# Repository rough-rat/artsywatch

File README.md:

# artsywatch

## Licensing Note

This project uses footprints, symbols and and 3D models converted via the
[easy2kicad](https://github.com/uPesy/easyeda2kicad.py) project.
These are derived from publicly available EasyEDA/JLCPCB component data,
used here solely to support reproducibility of this open hardware design.
All trademarks and component data belong to their respective owners.

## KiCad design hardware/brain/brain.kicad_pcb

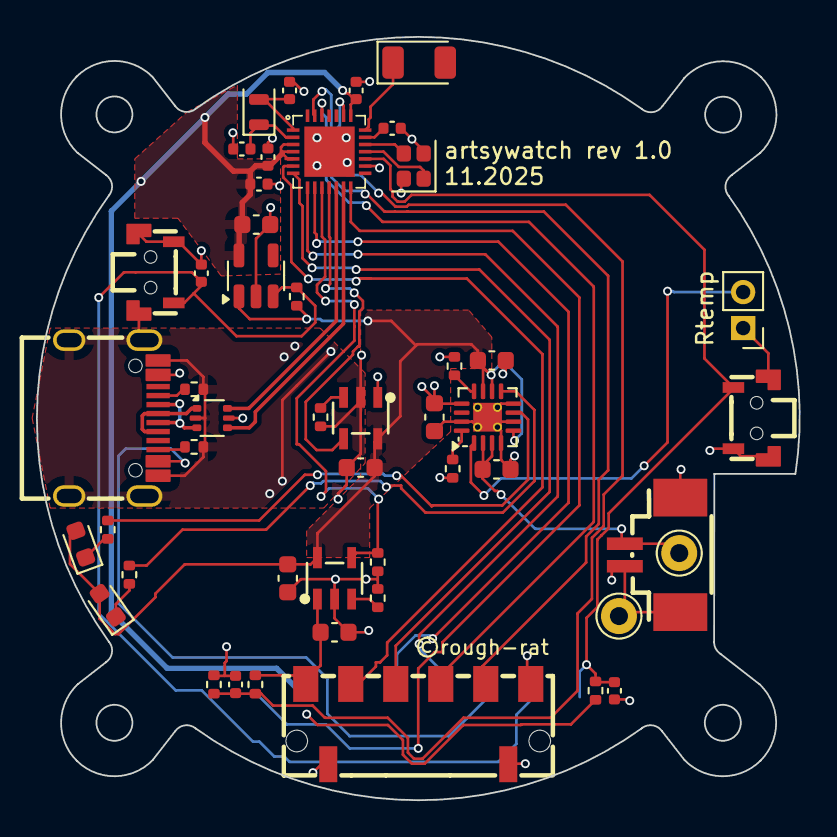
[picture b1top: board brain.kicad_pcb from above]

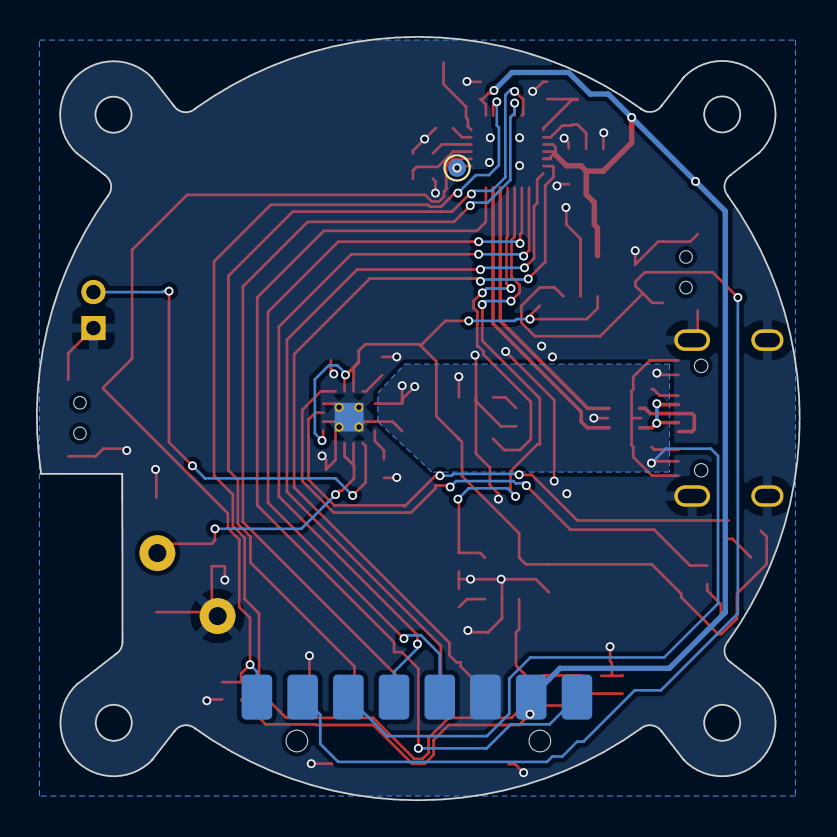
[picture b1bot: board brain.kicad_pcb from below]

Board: 2 copper layers, 42.4 x 42.4 mm, 50 parts (2 on the bottom side), 40 nets.

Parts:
AE1: Antenna_Chip; Johanson_2450AT18x100
C1, C4, C5, C6, C7, C8, C20: 10u; C_0603_1608Metric
C9, C13, C15, C17: 100n; C_0402_1005Metric
C11, C12, C14: 2.2uF; C_0402_1005Metric
C18, C19: 12p; C_0402_1005Metric
CN1: GT-BTP25006-0300A-010A; CONN-SMD_GT-BTP25006-0300A-010A
D1: LED_WHITE; LED_0603_1608Metric
D2: LED_RED; LED_0603_1608Metric
J5: Conn_01x08; PinSocket_1x08_P2.54mm_Vertical
P1: 1.25T-2PWT; CONN-SMD_P1.25-H_1.25T-2PWT
R1, R3: 5.1k; R_0402_1005Metric
R2, R4, R5, R12, R17, R20: 10k; R_0402_1005Metric
R6, R7: 3k; R_0402_1005Metric
R10, R11, R13: 100k; R_0402_1005Metric
SW1, SW2: TS24CA; SW-SMD_2P-TS24CA
TP1, TP2: TestPoint; Pin_D1.0mm_L10.0mm
TP3: TestPoint_2Pole; PinHeader_1x02_P2.00mm_Vertical
TP4: RX; TestPoint_Pad_D1.0mm
U1: USBLC6-2P6; SOT-666
U2: SPX3819M5-L-3-3; SOT-23-5
U3: BQ24073RGT; VQFN-16-1EP_3x3mm_P0.5mm_EP1.6x1.6mm_ThermalVias
U4, U5: LPW5209AB5F; SOT-23-5_L3.0-W1.7-P0.95-LS2.8-BL
U6: CH582F_C3001175; QFN-28_L4.0-W4.0-P0.40-BL-EP2.8
USBC1: TYPE-C-31-M-12; USB-C_SMD-TYPE-C-31-M-12_1
Y1: XO-32K; Crystal_SMD_2012-2Pin_2.0x1.2mm
Y2: 32 MHz; Crystal_SMD_2016-4Pin_2.0x1.6mm

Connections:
+4V: C4.1, C7.1, C20.1, D1.2 (A), D2.2 (A), R2.1, U2.1 (IN), U3.5 (EN2), U3.10 (OUT), U3.11 (OUT), U4.5 (VIN), U5.5 (VIN)
/4V_ENA: R11.2, U4.4 (EN), U6.10 (PB13/U2D+/SCK0_/SCL/TXD1_)
/4V_OUT: C8.1, CN1.1, R10.2, U4.1 (VOUT)
/BOOT: C17.1, J5.8, R17.1, SW2.1, U6.17 (PB22/TMR3/RXD2)
/BQ_CHG: R5.1, U3.9 (~CHG)
/BQ_PGOOD: R4.1, U3.7 (~PGOOD)
/CONN_DN: U1.3 (I/O2), USBC1.A7 (DN1), USBC1.B7 (DN2)
/CONN_DP: U1.1 (I/O1), USBC1.A6 (DP1), USBC1.B6 (DP2)
/DAT: CN1.4, U6.26 (PA14/MOSI/TXD0_/AIN4)
/LAT: CN1.3, U6.7 (PA9/TMR0/TXD1/AIN13)
/LIPO+: C6.1, P1.1, TP1.1, U3.2 (BAT), U3.3 (BAT)
/OE: CN1.2, U6.6 (PA8/RXD1/AIN12)
/PWR_CUTOFF: C15.1, J5.7, R2.2, SW1.1, U2.3 (EN)
/SCLK: CN1.5, U6.27 (PA13/SCK0/PWM5/AIN3)
/TCK: J5.5, U6.8 (PB15/TCK/MISO_/DTR_)
/TIO: J5.4, U6.9 (PB14/TIO/DSR_/MOSI_/PWM10)
/TX: J5.1, U6.14 (PB7/TXD0/PWM9)
/USB_BACKFEED_ENA: U5.4 (EN), U6.11 (PB12/U2D-/SCS_/SDA/RXD1_)
/USB_DN: U1.4 (I/O2), U6.13 (PB10/UD-/TMR1_)
/USB_DP: U1.6 (I/O1), U6.12 (PB11/UD+/TMR2_)
/VBAT_MEAS: C9.1, R10.1, R13.2, U6.23 (PA4/RXD3/AIN0)
/X32I: U6.19 (X32MI), Y2.3
/X32O: U6.18 (X32MO), Y2.1
/nRST: TP4.1, U6.16 (PB23/RST/TMR0_/TXD2_/PWM11)
GND: C1.2, C4.2, C5.2, C6.2, C7.2, C8.2, C9.2, C11.2, C12.2, C13.2, C14.1, C15.2, C17.2, C18.2, C19.2, C20.2, CN1.6, CN1.7, CN1.8, J5.3, P1.2, P1.3, P1.4, R1.2, R3.2, R6.1, R7.1, R11.1, R12.1, R13.1, R20.1, SW1.2, SW1.3, SW1.4, SW2.2, SW2.3, SW2.4, TP2.1, TP3.1, U1.2 (GND), U2.2 (GND), U3.4 (~CE), U3.6 (EN1), U3.8 (VSS), U3.15 (TD), U3.17 (VSS), U4.2 (GND), U5.2 (GND), U6.29 (EP), USBC1.1 (EH), USBC1.2 (EH), USBC1.3 (EH), USBC1.4 (EH), USBC1.A1B12 (GND), USBC1.B1A12 (GND), Y2.2, Y2.4
unnamed: AE1.1 (FEED), U6.21 (ANT)
unnamed: D1.1 (K), R4.2
unnamed: D2.1 (K), R5.2
unnamed: R6.2, U3.12 (ILIM)
unnamed: R7.2, U3.16 (ISET)
unnamed: TP3.2, U3.1 (TS)
unnamed: R12.2, U4.3 (ISET)
unnamed: R20.2, U5.3 (ISET)
unnamed: C18.1, U6.2 (PA10/X32KI/TMR1), Y1.1
unnamed: C19.1, U6.1 (PA11/X32KO/TMR2), Y1.2
unnamed: C14.2, U6.20 (VINTA)
unnamed: R3.1, USBC1.A5 (CC1)
unnamed: R1.1, USBC1.B5 (CC2)
VBUS: C1.1, J5.6, U1.5 (VBUS), U3.13 (IN), U5.1 (VOUT), USBC1.A4B9 (VBUS), USBC1.B4A9 (VBUS)
VDD: C5.1, C11.1, C12.1, C13.1, J5.2, R17.2, U2.5 (OUT), U6.3 (VDCID), U6.4 (VSW), U6.5 (VIO33/VDD33), U6.22 (VDCIA)

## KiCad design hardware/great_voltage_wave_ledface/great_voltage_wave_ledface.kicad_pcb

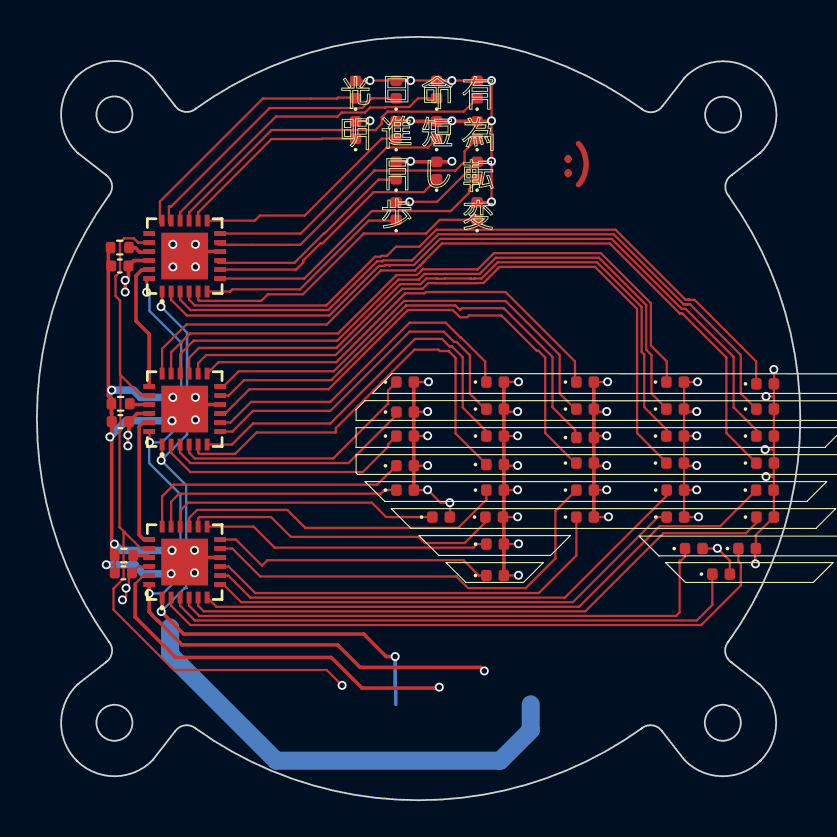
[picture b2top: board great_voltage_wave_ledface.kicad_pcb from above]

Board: 2 copper layers, 42.4 x 42.4 mm, 58 parts (1 on the bottom side), 59 nets.

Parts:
C3, C10, C16: 470n; C_0402_1005Metric
D3, D4, D5, D6, D7, D8, D9, D10, D11, D12, D13, D14, D15, D16, D17, D18, D19, D20, D21, D22, D23, D24, D25, D26, D27, D28, D29, D30, D31, D32, D33, D34, D35, D36, D37, D38, D39, D40, D41, D42, D43, D44, D45, D46, D47, D48, D49, D50: LED; LED_0402_1005Metric
J1: Conn_01x06; CONN-SMD_GT-BTP25006-0300A-010A
R14, R16, R19: 510; R_0402_1005Metric
U101, U102, U103: FM6126QC; TQFN-24_L4.0-W4.0-P0.50-BL-EP2.6

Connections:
/DAT: J1.4, U101.23 (SDI)
/LAT: J1.3, U101.1 (LE), U102.1 (LE), U103.1 (LE)
/OE: J1.2, U101.20 (OE), U102.20 (OE), U103.20 (OE)
/SCLK: J1.5, U101.24 (CLK), U102.24 (CLK), U103.24 (CLK)
GND: C3.2, C10.2, C16.2, J1.6, R14.2, R16.2, R19.2, U101.10 (GND), U101.25 (EP), U102.10 (GND), U102.25 (EP), U103.10 (GND), U103.25 (EP)
unnamed: D3.1 (K), U103.18 (~OUT15)
unnamed: D4.1 (K), U103.17 (~OUT14)
unnamed: D5.1 (K), U103.16 (~OUT13)
unnamed: D6.1 (K), U103.15 (~OUT12)
unnamed: D7.1 (K), U103.14 (~OUT11)
unnamed: D8.1 (K), U103.13 (~OUT10)
unnamed: D9.1 (K), U103.12 (~OUT9)
unnamed: D10.1 (K), U103.11 (~OUT8)
unnamed: D11.1 (K), U103.9 (~OUT7)
unnamed: D12.1 (K), U103.8 (~OUT6)
unnamed: D13.1 (K), U103.7 (~OUT5)
unnamed: D14.1 (K), U103.6 (~OUT4)
unnamed: D15.1 (K), U103.5 (~OUT3)
unnamed: D16.1 (K), U103.4 (~OUT2)
unnamed: D17.1 (K), U103.3 (~OUT1)
unnamed: D18.1 (K), U103.2 (~OUT0)
unnamed: D19.1 (K), U102.2 (~OUT0)
unnamed: D20.1 (K), U102.3 (~OUT1)
unnamed: D21.1 (K), U102.4 (~OUT2)
unnamed: D22.1 (K), U102.5 (~OUT3)
unnamed: D23.1 (K), U102.6 (~OUT4)
unnamed: D24.1 (K), U102.7 (~OUT5)
unnamed: D25.1 (K), U102.8 (~OUT6)
unnamed: D26.1 (K), U102.9 (~OUT7)
unnamed: D27.1 (K), U102.11 (~OUT8)
unnamed: D28.1 (K), U102.12 (~OUT9)
unnamed: D29.1 (K), U102.13 (~OUT10)
unnamed: D30.1 (K), U102.14 (~OUT11)
unnamed: D31.1 (K), U102.15 (~OUT12)
unnamed: D32.1 (K), U102.16 (~OUT13)
unnamed: D33.1 (K), U102.17 (~OUT14)
unnamed: D34.1 (K), U102.18 (~OUT15)
unnamed: D35.1 (K), U101.2 (~OUT0)
unnamed: D36.1 (K), U101.3 (~OUT1)
unnamed: D37.1 (K), U101.4 (~OUT2)
unnamed: D38.1 (K), U101.5 (~OUT3)
unnamed: D39.1 (K), U101.6 (~OUT4)
unnamed: D40.1 (K), U101.7 (~OUT5)
unnamed: D41.1 (K), U101.8 (~OUT6)
unnamed: D42.1 (K), U101.9 (~OUT7)
unnamed: D43.1 (K), U101.11 (~OUT8)
unnamed: D44.1 (K), U101.12 (~OUT9)
unnamed: D45.1 (K), U101.13 (~OUT10)
unnamed: D46.1 (K), U101.14 (~OUT11)
unnamed: D47.1 (K), U101.15 (~OUT12)
unnamed: D48.1 (K), U101.16 (~OUT13)
unnamed: D49.1 (K), U101.17 (~OUT14)
unnamed: D50.1 (K), U101.18 (~OUT15)
unnamed: R14.1, U101.21 (REXT)
unnamed: U101.19 (SDO), U102.23 (SDI)
unnamed: R16.1, U102.21 (REXT)
unnamed: U102.19 (SDO), U103.23 (SDI)
unnamed: R19.1, U103.21 (REXT)
VDD: C3.1, C10.1, C16.1, D3.2 (A), D4.2 (A), D5.2 (A), D6.2 (A), D7.2 (A), D8.2 (A), D9.2 (A), D10.2 (A), D11.2 (A), D12.2 (A), D13.2 (A), D14.2 (A), D15.2 (A), D16.2 (A), D17.2 (A), D18.2 (A), D19.2 (A), D20.2 (A), D21.2 (A), D22.2 (A), D23.2 (A), D24.2 (A), D25.2 (A), D26.2 (A), D27.2 (A), D28.2 (A), D29.2 (A), D30.2 (A), D31.2 (A), D32.2 (A), D33.2 (A), D34.2 (A), D35.2 (A), D36.2 (A), D37.2 (A), D38.2 (A), D39.2 (A), D40.2 (A), D41.2 (A), D42.2 (A), D43.2 (A), D44.2 (A), D45.2 (A), D46.2 (A), D47.2 (A), D48.2 (A), D49.2 (A), D50.2 (A), J1.1, U101.22 (VDD), U102.22 (VDD), U103.22 (VDD)

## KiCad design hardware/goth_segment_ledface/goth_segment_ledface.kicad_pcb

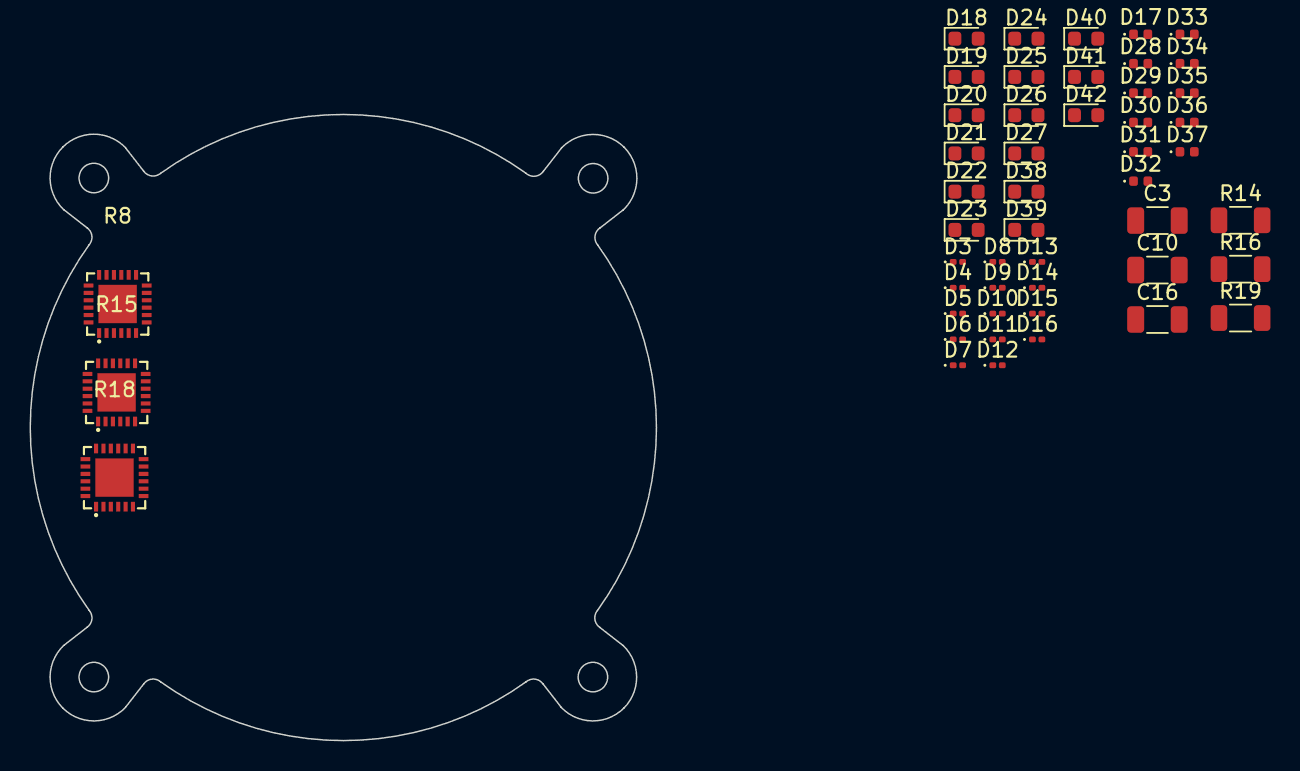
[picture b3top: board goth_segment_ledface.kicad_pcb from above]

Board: 2 copper layers, 42.4 x 42.4 mm, 49 parts (0 on the bottom side), 50 nets, no tracks yet.

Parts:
C3, C10, C16: 470n; C_1206_3216Metric
D3, D4, D5, D6, D7, D8, D9, D10, D11, D12, D13, D14, D15, D16: LED; LED_0201_0603Metric
D17, D28, D29, D30, D31, D32, D33, D34, D35, D36, D37: LED; LED_0402_1005Metric
D18, D19, D20, D21, D22, D23, D24, D25, D26, D27, D38, D39, D40, D41, D42: LED; LED_0603_1608Metric
R8, R15, R18: FM6126QC; TQFN-24_L4.0-W4.0-P0.50-BL-EP2.6
R14, R16, R19: 510; R_1206_3216Metric

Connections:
/LAT: R8.1 (LE), R15.1 (LE), R18.1 (LE)
/OE: R8.20 (OE), R15.20 (OE), R18.20 (OE)
/SCLK: R8.24 (CLK), R15.24 (CLK), R18.24 (CLK)
GND: C3.2, C10.2, C16.2, R8.10 (GND), R8.25 (EP), R14.2, R15.10 (GND), R15.25 (EP), R16.2, R18.10 (GND), R18.25 (EP), R19.2
unnamed: D3.2 (A), R8.2 (~OUT0)
unnamed: D4.2 (A), R8.3 (~OUT1)
unnamed: D5.2 (A), R8.4 (~OUT2)
unnamed: D6.2 (A), R8.5 (~OUT3)
unnamed: D7.2 (A), R8.6 (~OUT4)
unnamed: D8.2 (A), R8.7 (~OUT5)
unnamed: D9.2 (A), R8.8 (~OUT6)
unnamed: D10.2 (A), R8.9 (~OUT7)
unnamed: D11.2 (A), R8.11 (~OUT8)
unnamed: D12.2 (A), R8.12 (~OUT9)
unnamed: D13.2 (A), R8.13 (~OUT10)
unnamed: D14.2 (A), R8.14 (~OUT11)
unnamed: D15.2 (A), R8.15 (~OUT12)
unnamed: D16.2 (A), R8.16 (~OUT13)
unnamed: D17.2 (A), R8.17 (~OUT14)
unnamed: D18.2 (A), R8.18 (~OUT15)
unnamed: D19.2 (A), R15.2 (~OUT0)
unnamed: D20.2 (A), R15.3 (~OUT1)
unnamed: D21.2 (A), R15.4 (~OUT2)
unnamed: D22.2 (A), R15.5 (~OUT3)
unnamed: D23.2 (A), R15.6 (~OUT4)
unnamed: D24.2 (A), R15.7 (~OUT5)
unnamed: D25.2 (A), R15.8 (~OUT6)
unnamed: D26.2 (A), R15.9 (~OUT7)
unnamed: D27.2 (A), R15.11 (~OUT8)
unnamed: D28.2 (A), R15.12 (~OUT9)
unnamed: D29.2 (A), R15.13 (~OUT10)
unnamed: D30.2 (A), R15.14 (~OUT11)
unnamed: D31.2 (A), R15.15 (~OUT12)
unnamed: D32.2 (A), R15.16 (~OUT13)
unnamed: D33.2 (A), R15.17 (~OUT14)
unnamed: D34.2 (A), R15.18 (~OUT15)
unnamed: D35.2 (A), R18.2 (~OUT0)
unnamed: D36.2 (A), R18.3 (~OUT1)
unnamed: D37.2 (A), R18.4 (~OUT2)
unnamed: D38.2 (A), R18.5 (~OUT3)
unnamed: D39.2 (A), R18.6 (~OUT4)
unnamed: D40.2 (A), R18.7 (~OUT5)
unnamed: D41.2 (A), R18.8 (~OUT6)
unnamed: D42.2 (A), R18.9 (~OUT7)
unnamed: R8.21 (REXT), R14.1
unnamed: R15.21 (REXT), R16.1
unnamed: R8.19 (SDO), R15.23 (SDI)
unnamed: R15.19 (SDO), R18.23 (SDI)
unnamed: R18.21 (REXT), R19.1
VDD: C3.1, C10.1, C16.1, R8.22 (VDD), R15.22 (VDD), R18.22 (VDD)

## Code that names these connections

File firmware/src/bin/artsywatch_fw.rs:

#![feature(impl_trait_in_assoc_type)]
#![feature(type_alias_impl_trait)]
#![feature(generic_const_exprs)]
#![no_std]
#![no_main]

use ch58x_hal as hal;
use embassy_executor::Spawner;
use hal::gpio::{Level, Output, OutputDrive};
use hal::peripherals;
use hal::uart::UartTx;
use hal::ble;
use ch58x_rs_kit::logger::init as init_logger;
use ch58x_rs_kit::{get_configured_rtc, log, tmos_mainloop};
use ch58x_rs_kit::sr_led_driver::SrLedDriver;
use ledface_layout::Layout;

use ch58x_rs_kit::ble_periph::{common_init, devinfo_init, peripheral};
use ch58x_rs_kit::ble_periph::current_time_service::current_time_init;

use embassy_time::Duration;
use embassy_time::Timer;
use ch58x_hal::gpio::AnyPin;

const TEST_LAYOUT_JSON: &[u8] = include_bytes!(concat!(
    env!("CARGO_MANIFEST_DIR"),
    "/ledface_layout/test/test.json"
));
const COMPILED_LAYOUT_BYTES: &[u8] =
    include_bytes!(concat!(env!("OUT_DIR"), "/watchface_layout.bin"));

type WatchLayout = Layout<48, 4, 48>;

fn load_layout() -> Option<WatchLayout> {
    match Layout::from_bytes(COMPILED_LAYOUT_BYTES) {
        Ok(layout) => Some(layout),
        Err(_) => Layout::from_json(TEST_LAYOUT_JSON).ok(),
    }
}

#[embassy_executor::task]
async fn async_blink(pin: AnyPin) {
    let mut led = Output::new(pin, Level::Low, OutputDrive::_5mA);

    loop {
        led.set_high();
        Timer::after(Duration::from_millis(150)).await;
        led.set_low();
        Timer::after(Duration::from_millis(150)).await;
    }
}

#[embassy_executor::task]
async fn sr_driver_task(mut sr_driver: SrLedDriver<'static, peripherals::SPI0, 48>) -> ! {
    log!("Shift register driver task started");
    sr_driver.enable_output();
    let mut layout = load_layout();
    if let Some(ref layout) = layout {
        log!(
            "Loaded LED layout: {} LEDs, {} entities",
            layout.led_count(),
            layout.entities.len()
        );
    } else {
        log!("Layout unavailable, using direct LED writes");
    }

    let mut frame = [0u8; 48];
    let mut text_angle: u16 = 0;
    let mut wave_angle: u16 = 0;
    let mut direct_index: usize = 0;
    let mut iteration: u32 = 0;
    loop {
        iteration = iteration.wrapping_add(1);

        if let Some(layout_ref) = layout.as_ref() {
            frame.fill(0);

            if let Some(text) = layout_ref.entity("Text") {
                text.set_degrees(text_angle, &mut frame);
            }
            if let Some(wave) = layout_ref.entity("Wave") {
                wave.set_degrees(wave_angle, &mut frame);
            }

            text_angle = (text_angle + 5) % 360;
            wave_angle = (wave_angle + 5) % 360;

            if let Err(err) = sr_driver.write(0, &frame) {
                log!("Frame write error {:?}, switching to direct mode", err);
                layout = None;
                continue;
            }
        // } else {
            // sr_driver.clear();
            // sr_driver
            //     .set_led(direct_index, 0xFF)
            //     .expect("direct LED index out of range");

            // direct_index = (direct_index + 1) % sr_driver.len();
        }

        log!("SR iteration {}", iteration);
        sr_driver.update();
        Timer::after(Duration::from_millis(200)).await;
    }
}

#[embassy_executor::main(entry = "qingke_rt::entry")]
async fn main(spawner: Spawner) -> ! {
    let mut config = hal::Config::default();
    config.clock.use_pll_60mhz().enable_lse();
    let p = hal::init(config);
    hal::embassy::init();

    let mut ena = Output::new(p.PB13, Level::Low, OutputDrive::_5mA);
    ena.set_high();

    let serial = UartTx::new(p.UART0, p.PB7, Default::default()).unwrap();
    init_logger(serial);
    log!("\n\n\nArtsyWatch Firmware Started!");

    // Shift register control pins for LED matrix column driving
    // SCK - PA13 (SPI Clock)
    // DAT - PA14 (SPI MOSI/Data)
    // OE  - PA8  (Output Enable, directly GPIO-controlled)
    // LAT - PA9  (Latch, directly GPIO-controlled)

    // Initialize shift register LED driver from pins
    let mut sr_driver =
        SrLedDriver::<_, 48>::new_from_pins::<false, _, _, _, _>(p.SPI0, p.PA13, p.PA14, p.PA8, p.PA9);

    log!("Shift register driver initialized");
    log!("  SPI: SCK=PA13, DAT=PA14");
    log!("  GPIO: OE=PA8, LAT=PA9");

    // Quick connectivity check before starting the main task.
    // sr_driver.test_write(0xFF);
    // sr_driver.test_write(0x00);
    // log!("Starting shift register background task...");
    // spawner.spawn(sr_driver_task(sr_driver)).unwrap();

    let rtc = get_configured_rtc();

    log!("System Clocks: {}", hal::sysctl::clocks().hclk);
    log!("ChipID: 0x{:02x}", hal::signature::get_chip_id());
    log!("RTC datetime: {}", rtc.now());

    log!("BLE Lib Version: {}", ble::lib_version());

    let mut ble_config = ble::Config::default();
    ble_config.pa_config = None;
    ble_config.mac_addr = [0x21, 0x37, 0x04, 0x20, 0x69, 0x96].into();
    let (task_id, sub) = hal::ble::init(ble_config).unwrap();
    log!("BLE hal task id: {}", task_id);

    // loop {
    //     Timer::after(Duration::from_secs(1)).await;
    //     log!("Heartbeat: main alive");
    // }

    unsafe {
        common_init();
        devinfo_init();
        current_time_init();
    }

    // Main_Circulation
    spawner.spawn(tmos_mainloop()).unwrap();

    // Application code
    peripheral(spawner, task_id, sub, rtc, None).await
}

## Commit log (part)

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2025-10-18 @tym2k1 you go
2025-10-18 chore: move project to separate dir
2025-10-19 feat: add FM6126QC via easyeda2kicad
2025-10-19 fix: make FM6126QC 3D model work
2025-10-19 feat: modify FM6126QC footprint
2025-10-19 feat: use the project's FM6126QC
2025-10-19 feat: add Project Symbols/Footprints
2025-10-19 feat: fix symbol/footprint naming to more standarized
2025-10-19 chore: make git track 3D files
2025-10-19 feat: modify CH582F footprint
2025-10-19 feat: add CH582F via easyeda2kicad
2025-10-19 fix: flip the exported CH582F model
2025-10-19 feat: add SS-3292S-L2-B via easyeda2kicad
2025-10-19 feat: add TS24CA via easyeda2kicad
2025-10-19 feat: change switches to TS24CA
2025-10-19 chore: disable GT-USB-7055E USB-C, to be replaced
2025-10-20 feat: add goth segment display elements
2025-10-20 feat: initial pcb design
2025-10-20 feat: initial led placement
2025-10-21 fix: change watchface size to proper radius
    Was in diameter not radius
2025-10-21 feat: initial great voltage wave watchface
2025-10-23 feat: improved great voltage wave watchface
2025-10-23 feat: add TYPE-C-31-M-12 via easyeda2kicad
2025-10-23 feat: swap USB-C port for TYPE-C-31-M-12
2025-10-23 feat: great voltage wave change poem and touch up
2025-10-23 feat: great voltage wave PoC led placement
2025-10-26 revert: add accidentaly deleted F.Mask to great voltage wave
2025-11-05 copy some stuff from tama, support
2025-11-07 feat: don't populate LED's and register from schematic (2nd board)
2025-11-07 feat: add C2834312 via easyeda2kicad
2025-11-07 feat: initial placement
2025-11-07 feat: add initial screw-holes
2025-11-12 chore: separate into different KiCad projects
2025-11-13 route wawatchbrain
2025-11-19 feat: improved screw holes
2025-11-19 chore: fix 3D models rendering
2025-11-19 fix: fix footprint/symbol libs project paths
2025-11-19 feat: initial ledface/brain connector
2025-11-20 feat: great voltage wave final led placement
2025-11-22 brain order prepared
2025-11-22 voltage wave initial routing
2025-11-22 voltage wave routed
2025-11-22 forgor save pcb file
2025-12-20 fix: correct 3d models placement
2026-01-04 feat(voltage wave): add screw-holes to watchface (same size as brain/ledface)
2026-03-21 chore: kanji_poem.svg -> kanji.svg add variations used on watch

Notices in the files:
hardware/brain/brain.kicad_pcb:
©rough-rat
